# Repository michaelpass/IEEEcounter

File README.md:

# IEEEcounter
UIowa IEEE binary counter project

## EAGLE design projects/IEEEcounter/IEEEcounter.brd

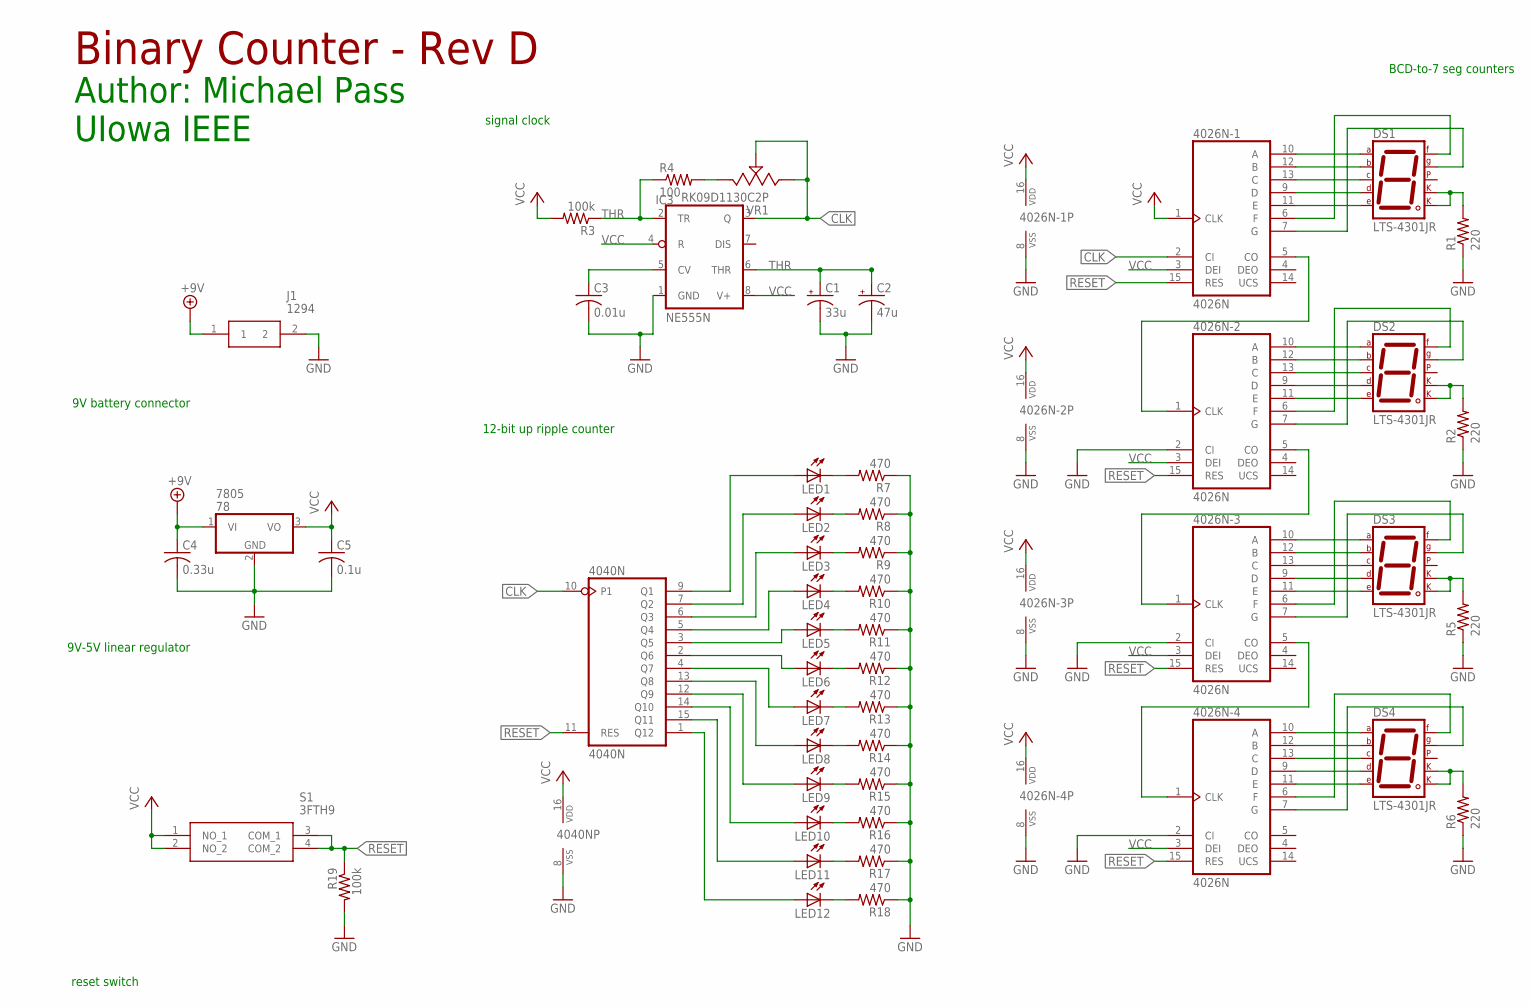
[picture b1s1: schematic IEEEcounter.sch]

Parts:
4026N-1, 4026N-2, 4026N-3, 4026N-4: 4026N; DIL16
4040N: 4040N; DIL16
7805: 78; TO220H
C1: 33u; E2,5-6
C2: 47u; E2,5-6
C3: 0.01u; C050-025X075
C4: 0.33u; C1210
C5: 0.1u; C1210
DS1, DS2, DS3, DS4: LTS-4301JR; DIPS762W50P254L1290H700Q10N
IC3: NE555N; DIL08
J1: 1294
LED1, LED2, LED3, LED4, LED5, LED6, LED7, LED8, LED9, LED10, LED11, LED12: LED5MM
R1, R2, R5, R6: 220; R1210
R3, R19: 100k; R1210
R4: 100; R1210
R7, R8, R9, R10, R11, R12, R13, R14, R15, R16, R17, R18: 470; R1210
S1: 3FTH9
VR1: RK09D1130C2P; RK09D1130C3C

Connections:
+9V: 7805.1 (VI), C4.1, J1.1
CLK: 4026N-1.2 (CI), 4040N.10 (P1), IC3.3 (Q), VR1.2, VR1.3
GND: 4026N-1.8 (VSS), 4026N-2.2 (CI), 4026N-2.8 (VSS), 4026N-3.2 (CI), 4026N-3.8 (VSS), 4026N-4.2 (CI), 4026N-4.8 (VSS), 4040N.8 (VSS), 7805.2 (GND), C1.-, C2.-, C3.2, C4.2, C5.2, IC3.1 (GND), J1.2, R1.1, R2.1, R5.1, R6.1, R7.1, R8.1, R9.1, R10.1, R11.1, R12.1, R13.1, R14.1, R15.1, R16.1, R17.1, R18.1, R19.2
unnamed: 4026N-1.6 (F), DS1.2 (F)
unnamed: 4026N-1.7 (G), DS1.1 (G)
unnamed: 4026N-1.10 (A), DS1.10 (A)
unnamed: 4026N-1.12 (B), DS1.9 (B)
unnamed: 4026N-1.13 (C), DS1.7 (C)
unnamed: 4026N-1.9 (D), DS1.5 (D)
unnamed: 4026N-1.11 (E), DS1.4 (E)
unnamed: DS1.3 (CK1), DS1.8 (CK2), R1.2
unnamed: R4.2, VR1.1
unnamed: C3.1, IC3.5 (CV)
unnamed: LED11.K (C), R17.2
unnamed: 4040N.9 (Q1), LED1.A
unnamed: 4040N.7 (Q2), LED2.A
unnamed: 4040N.6 (Q3), LED3.A
unnamed: 4040N.5 (Q4), LED4.A
unnamed: LED12.K (C), R18.2
unnamed: LED10.K (C), R16.2
unnamed: LED9.K (C), R15.2
unnamed: LED8.K (C), R14.2
unnamed: LED7.K (C), R13.2
unnamed: LED6.K (C), R12.2
unnamed: LED5.K (C), R11.2
unnamed: LED4.K (C), R10.2
unnamed: LED3.K (C), R9.2
unnamed: LED2.K (C), R8.2
unnamed: LED1.K (C), R7.2
unnamed: 4040N.3 (Q5), LED5.A
unnamed: 4040N.2 (Q6), LED6.A
unnamed: 4040N.4 (Q7), LED7.A
unnamed: 4040N.13 (Q8), LED8.A
unnamed: 4040N.12 (Q9), LED9.A
unnamed: 4040N.14 (Q10), LED10.A
unnamed: 4040N.15 (Q11), LED11.A
unnamed: 4040N.1 (Q12), LED12.A
unnamed: 4026N-2.6 (F), DS2.2 (F)
unnamed: 4026N-2.7 (G), DS2.1 (G)
unnamed: 4026N-2.10 (A), DS2.10 (A)
unnamed: 4026N-2.12 (B), DS2.9 (B)
unnamed: 4026N-2.13 (C), DS2.7 (C)
unnamed: 4026N-2.9 (D), DS2.5 (D)
unnamed: 4026N-2.11 (E), DS2.4 (E)
unnamed: DS2.3 (CK1), DS2.8 (CK2), R2.2
unnamed: 4026N-3.6 (F), DS3.2 (F)
unnamed: 4026N-3.7 (G), DS3.1 (G)
unnamed: 4026N-3.10 (A), DS3.10 (A)
unnamed: 4026N-3.12 (B), DS3.9 (B)
unnamed: 4026N-3.13 (C), DS3.7 (C)
unnamed: 4026N-3.9 (D), DS3.5 (D)
unnamed: 4026N-3.11 (E), DS3.4 (E)
unnamed: DS3.3 (CK1), DS3.8 (CK2), R5.2
unnamed: 4026N-4.6 (F), DS4.2 (F)
unnamed: 4026N-4.7 (G), DS4.1 (G)
unnamed: 4026N-4.10 (A), DS4.10 (A)
unnamed: 4026N-4.12 (B), DS4.9 (B)
unnamed: 4026N-4.13 (C), DS4.7 (C)
unnamed: 4026N-4.9 (D), DS4.5 (D)
unnamed: 4026N-4.11 (E), DS4.4 (E)
unnamed: DS4.3 (CK1), DS4.8 (CK2), R6.2
unnamed: 4026N-1.5 (CO), 4026N-2.1 (CLK)
unnamed: 4026N-2.5 (CO), 4026N-3.1 (CLK)
unnamed: 4026N-3.5 (CO), 4026N-4.1 (CLK)
RESET: 4026N-1.15 (RES), 4026N-2.15 (RES), 4026N-3.15 (RES), 4026N-4.15 (RES), 4040N.11 (RES), R19.1, S1.3 (COM_1), S1.4 (COM_2)
THR: C1.+, C2.+, IC3.2 (TR), IC3.6 (THR), R3.1, R4.1
VCC: 4026N-1.1 (CLK), 4026N-1.3 (DEI), 4026N-1.16 (VDD), 4026N-2.3 (DEI), 4026N-2.16 (VDD), 4026N-3.3 (DEI), 4026N-3.16 (VDD), 4026N-4.3 (DEI), 4026N-4.16 (VDD), 4040N.16 (VDD), 7805.3 (VO), C5.1, IC3.4 (R), IC3.8 (V+), R3.2, S1.1 (NO_1), S1.2 (NO_2)

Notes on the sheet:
Binary Counter - Rev D
Author: Michael Pass
UIowa IEEE
9V battery connector
9V-5V linear regulator
reset switch
signal clock
12-bit up ripple counter
BCD-to-7 seg counters

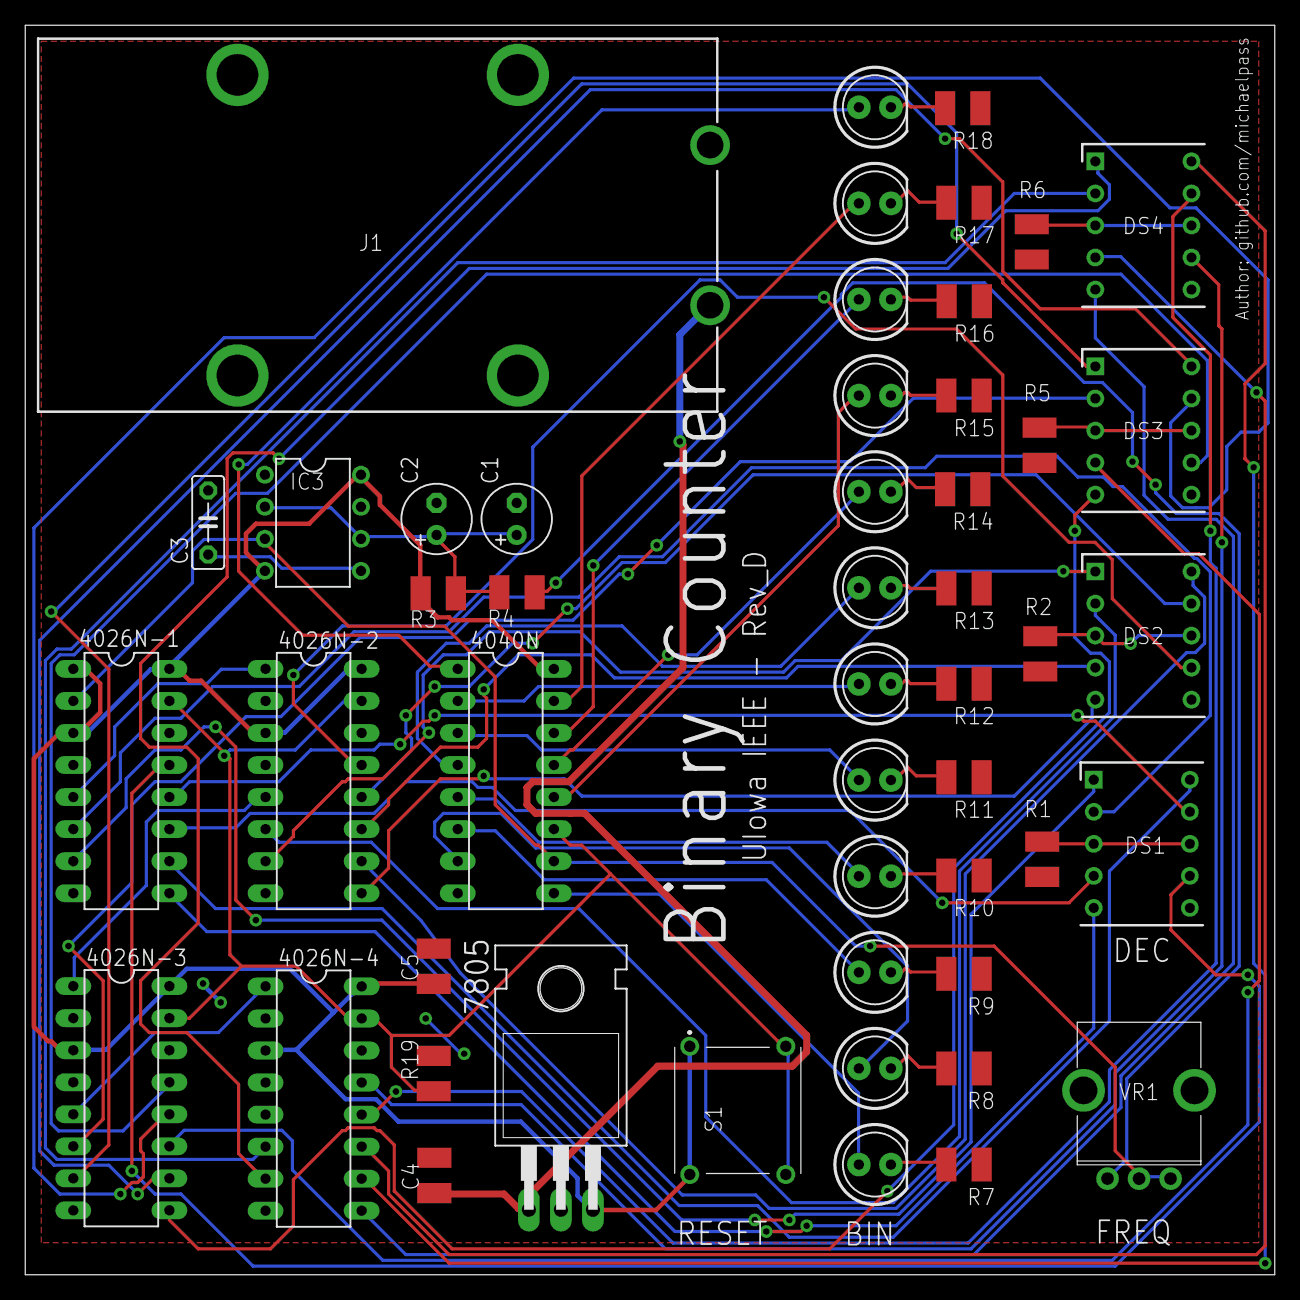
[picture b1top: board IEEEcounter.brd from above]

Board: 2 copper layers, 99.1 x 99.1 mm, 50 parts (0 on the bottom side), 67 nets.

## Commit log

2019-10-01 Initial commit.
2019-10-01 Added Datasheets
2019-10-02 Added presentation

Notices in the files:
parts and their libraries:
SparkFun: Licensing: CC v3.0 Share-Alike You are welcome to use this library for commercial purposes.
